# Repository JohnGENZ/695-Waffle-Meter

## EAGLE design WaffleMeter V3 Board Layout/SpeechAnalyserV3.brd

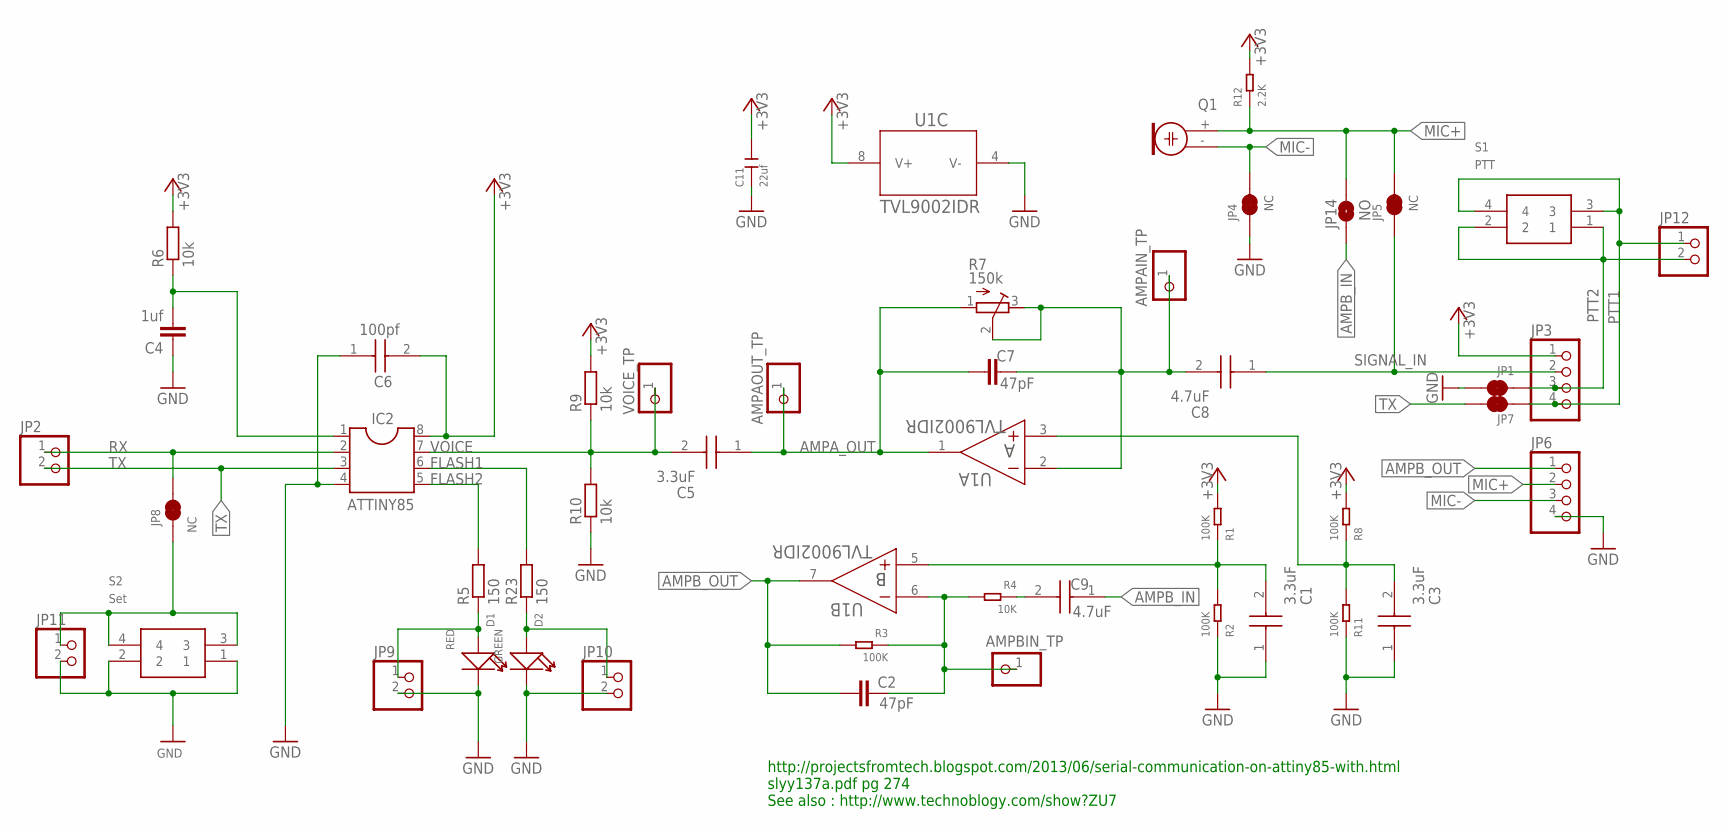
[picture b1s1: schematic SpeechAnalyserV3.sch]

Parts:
AMPA_IN: AMPAIN_TP; 1X01
AMPA_OUT: AMPAOUT_TP; 1X01
AMPB_IN: AMPBIN_TP; 1X01
C1, C3, C5: 3.3uF; CAPC2013X140N
C2, C7: 47pF; C0805
C4: 1uf; C0805
C6: 100pf; CAPC2012X90N
C8, C9: 4.7uF; CAPC2013X140N
C11: 22uf; C1206
D1: RED; LED-0805
D2: GREEN; LED-0805
IC2: ATTINY85; SOCKET-08
JP1, JP4, JP5, JP7, JP8: NC; SMT-JUMPER_2_NC_TRACE_SILK
JP2, JP9, JP10, JP11, JP12: PINHD-1X2; 1X02
JP3, JP6: PINHD-1X4; 1X04
JP14: NO; SMT-JUMPER_2_NO_SILK
Q1: ELECTRET; 9.7ELECTRET
R1, R2, R3, R8, R11: 100K; R0805
R4: 10K; R0805
R5, R23: 150; R0805
R6, R9, R10: 10k; R0805
R7: 150k; RTRIM64W
R12: 2.2K; R0805
S1: PTT; B3FS-1000P
S2: Set; B3FS-1000P
U1: TVL9002IDR; D0008A_N
VOICE: VOICE_TP; 1X01

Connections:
+3V3: C6.2, C11.2, IC2.8, JP3.1, R1.2, R6.2, R8.2, R9.2, R12.2, U1.8 (V+)
AMPA_OUT: AMPA_OUT.1, C5.1 (C1), C7.1, R7.1 (A), U1.1 (OUT)
AMPB_IN: C9.1 (C1), JP14.1
AMPB_OUT: C2.1, JP6.1, R3.2, U1.7 (OUT)
FLASH1: IC2.6, R23.2
FLASH2: IC2.5, R5.2
GND: C1.1 (C1), C3.1 (C1), C4.1, C6.1, C11.1, D1.-, D2.-, IC2.4, JP1.1, JP4.1, JP6.4, JP9.2, JP10.2, JP11.2, R2.1, R10.1, R11.1, S2.1, S2.2, U1.4 (V-)
MIC+: JP5.2, JP6.2, JP14.2, Q1.+ (2), R12.1
MIC-: JP4.2, JP6.3, Q1.- (1)
unnamed: C9.2 (C2), R4.1
unnamed: C3.2 (C2), R8.1, R11.2, U1.3 (IN+)
unnamed: C1.2 (C2), R1.1, R2.2, U1.5 (IN+)
unnamed: AMPB_IN.1, C2.2, R3.1, R4.2, U1.6 (IN-)
unnamed: D1.+, JP9.1, R5.1
unnamed: D2.+, JP10.1, R23.1
unnamed: AMPA_IN.1, C7.2, C8.2 (C2), R7.2 (S), R7.3 (E), U1.2 (IN-)
unnamed: C4.2, IC2.1, R6.1
unnamed: JP8.1, JP11.1, S2.3, S2.4
PTT1: JP3.4, JP7.2, JP12.1, S1.3, S1.4
PTT2: JP1.2, JP3.3, JP12.2, S1.1, S1.2
RX: IC2.2, JP2.1, JP8.2
SIGNAL_IN: C8.1 (C1), JP3.2, JP5.1
TX: IC2.3, JP2.2, JP7.1
VOICE: C5.2 (C2), IC2.7, R9.1, R10.2, VOICE.1

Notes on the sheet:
http://projectsfromtech.blogspot.com/2013/06/serial-communication-on-attiny85-with.html slyy137a.pdf pg 274 See also : http://www.technoblogy.com/show?ZU7

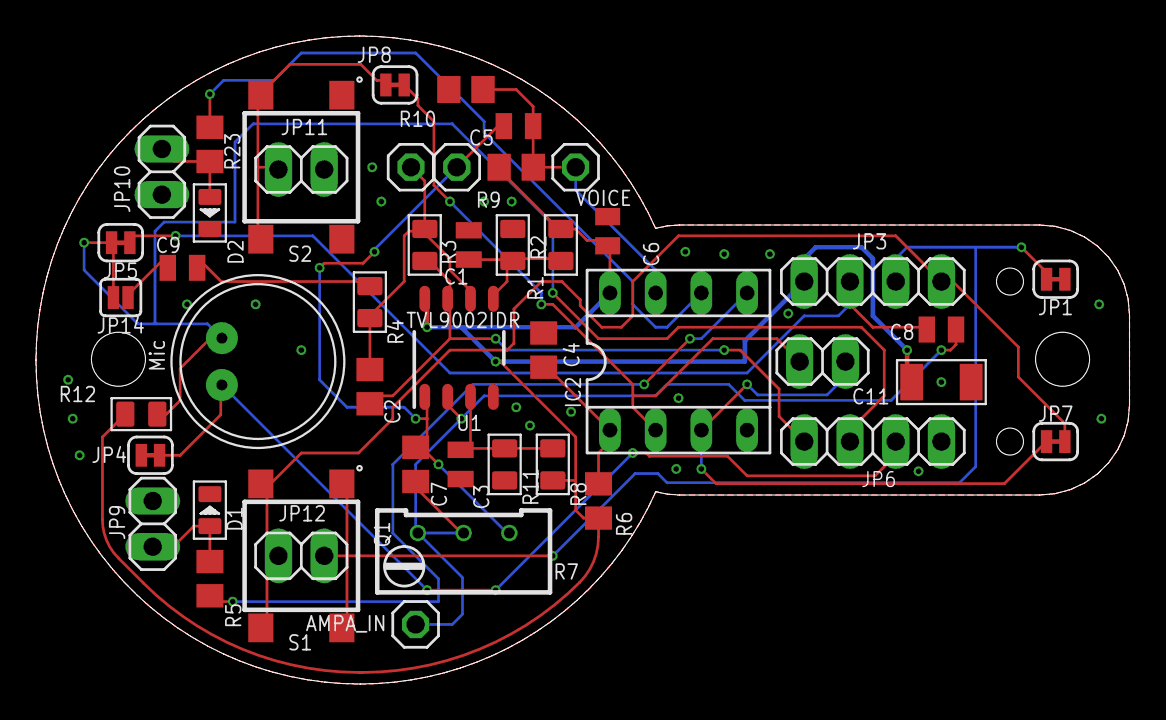
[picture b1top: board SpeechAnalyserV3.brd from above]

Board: 4 copper layers, 60.8 x 36.0 mm, 47 parts (0 on the bottom side), 24 nets.

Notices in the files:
parts and their libraries:
SparkFun-Jumpers: Licensing: Creative Commons ShareAlike 4.0 International - https://creativecommons.org/licenses/by-sa/4.0
